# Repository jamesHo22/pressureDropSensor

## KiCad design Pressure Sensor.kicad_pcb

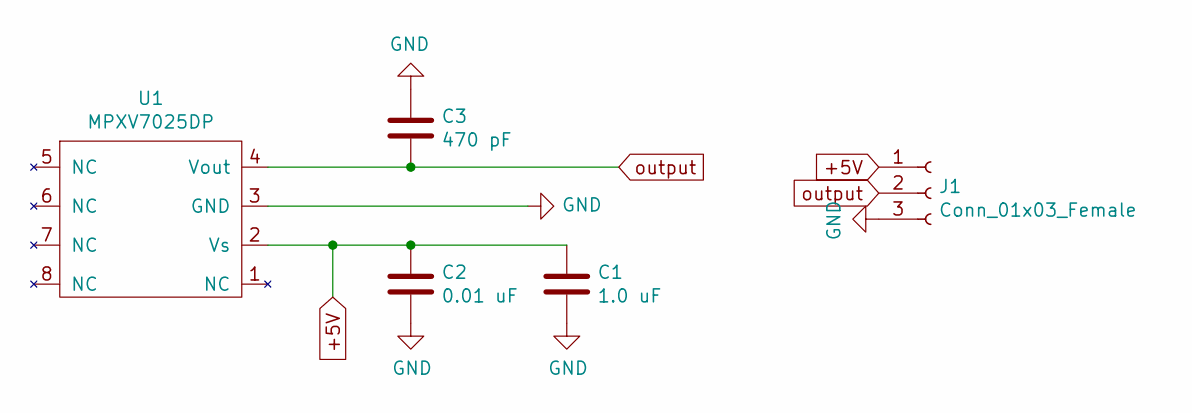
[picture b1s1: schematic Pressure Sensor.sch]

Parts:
C1: 1.0 uF; C_0805_2012Metric_Pad1.15x1.40mm_HandSolder
C2: 0.01 uF; C_0805_2012Metric_Pad1.15x1.40mm_HandSolder
C3: 470 pF; C_0805_2012Metric_Pad1.15x1.40mm_HandSolder
J1: Conn_01x03_Female; PinSocket_1x03_P2.54mm_Vertical
U1: MPXV7025DP

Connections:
+5V: C1.1, C2.1, J1.1, U1.2 (Vs)
GND: C1.2, C2.2, C3.1, J1.3, U1.3 (GND)
output: C3.2, J1.2, U1.4 (Vout)

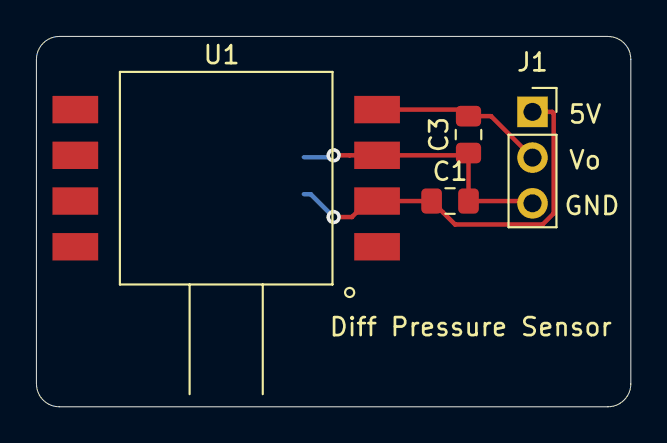
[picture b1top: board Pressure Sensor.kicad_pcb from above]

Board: 2 copper layers, 33.0 x 20.6 mm, 5 parts (1 on the bottom side), 3 nets.

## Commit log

2020-11-06 init commit
2020-11-09 updated caps
2020-11-09 moved GBR files into folder
